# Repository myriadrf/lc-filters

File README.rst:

LibreCellular RF Filter Designs
===============================

.. image:: https://raw.githubusercontent.com/myriadrf/lc-filters/main/images/B3LPD_0p1_PCB_1_1280w.jpg
   :alt: B3LPD prototype.

This repository contains the LibreCellular reference clock PCB (KiCAD) designs.

B3LPD
-----

LTE Band 3 (1800 MHz) low power duplexer. 

For further details see the `LibreCellular Documentation`_.

Licence
-------

LibreCellular RF Filter Designs is copyright 2023 AB Open Ltd and provided under the Solderpad Hardware License v2.1.

.. _LibreCellular Documentation: https://librecellular.org/developer/hardware/rf/b3lpd.html

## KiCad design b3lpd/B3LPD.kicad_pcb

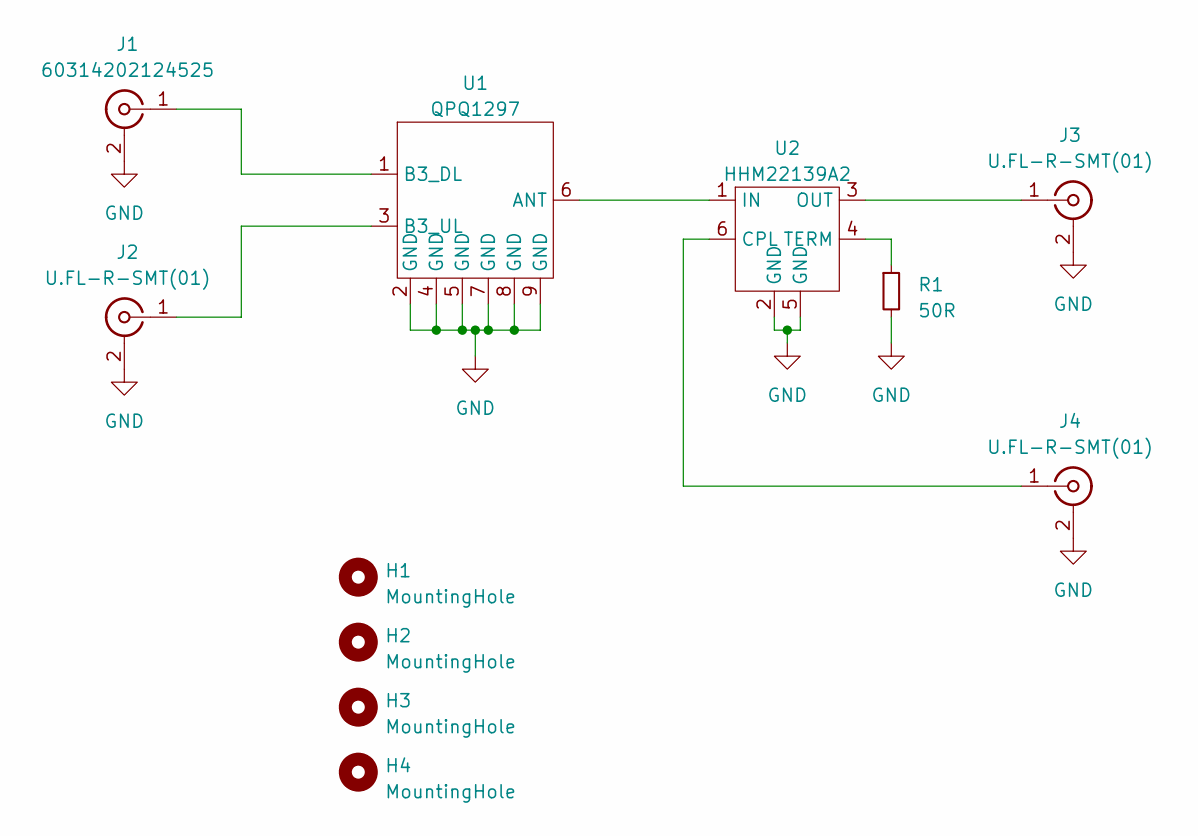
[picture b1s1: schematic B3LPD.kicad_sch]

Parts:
H1, H2, H3, H4: MountingHole; MountingHole_2.7mm_M2.5_ISO14580
J1: 60314202124525; Wurth_60314202124525; ManufacturerPartNumber 60314202124525
J2, J3, J4: U.FL-R-SMT(01); Connector_RF_Hirose_U.FL-R-SMT(01); ManufacturerPartNumber U.FL-R-SMT(01)
R1: 50R; R_0603_1608Metric
U1: QPQ1297; Qorvo_QPQ1297; ManufacturerPartNumber QPQ1297
U2: HHM22139A2; TDK_HHM22139A2; ManufacturerPartNumber HHM22139A2

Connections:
GND: J1.2 (Ext), J2.2 (Ext), J3.2 (Ext), J4.2 (Ext), R1.2, U1.2 (GND), U1.4 (GND), U1.5 (GND), U1.7 (GND), U1.8 (GND), U1.9 (GND), U2.2 (GND), U2.5 (GND)
unnamed: J1.1 (In), U1.1 (B3_DL)
unnamed: J2.1 (In), U1.3 (B3_UL)
unnamed: J3.1 (In), U2.3 (OUT)
unnamed: J4.1 (In), U2.6 (CPL)
unnamed: U1.6 (ANT), U2.1 (IN)
unnamed: R1.1, U2.4 (TERM)

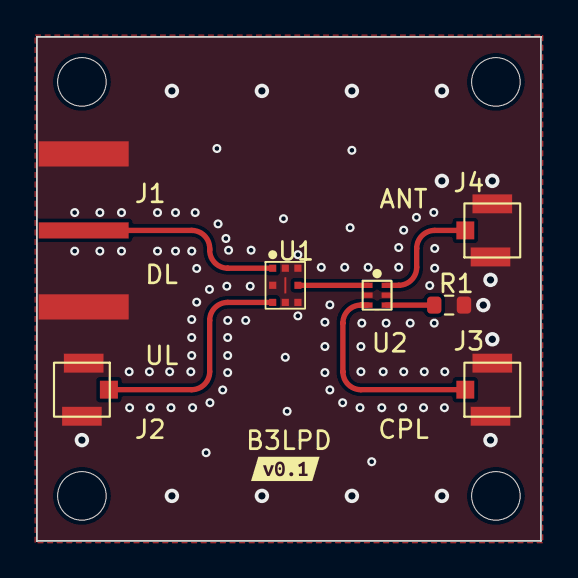
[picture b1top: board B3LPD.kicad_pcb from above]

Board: 4 copper layers, 28.0 x 28.0 mm, 13 parts (1 on the bottom side), 7 nets.

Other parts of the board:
Ref**: Val**; LibreCellular_PCB_GraphicOnly
kibuzzard-64104D25: G***; kibuzzard-64104D25

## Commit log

2023-08-11 Add B3LPD
2024-01-13 Add README.
2024-01-13 Fix image URL.
